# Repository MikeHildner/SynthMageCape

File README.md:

# Synth Mage Cape

An LED stage cape for a keyboard player. The lights follow what is played: a
small controller in a belt pouch listens to the keyboard over Bluetooth MIDI
and drives addressable LEDs on the lapels, the collar, the shoulders, and
strings of small lights below the lapels.

The picture is a concept render, not a photograph. A short video of the real
lights on a stand-in cape, following the keyboard: https://youtu.be/IYe8foX2Wks

## Where the project stands (November 2026)

- **Working:** the controller, the firmware, and every light, as a prototype
  on a stand-in cape.
- **Not made yet:** the cape itself. The sheet for the cape maker is
  [docs/designer-handoff.md](docs/designer-handoff.md).
- **Still changing.** This is the record of one build in progress, by a
  software developer who was new to electronics when it started. It is not a
  tested kit. Check the wiring, the power and your own parts before you copy
  anything.

## How it works

- **Keyboard:** a Korg Kronos with a CME WIDI Master in its MIDI OUT, which
  sends what is played as Bluetooth MIDI. Any keyboard that sends Bluetooth
  MIDI should do.
- **Controller:** an ESP32-S3 DevKitC-1 (N16R8) on a small board with a
  74AHCT125 level shifter, powered by a USB power bank. Four data outputs.
- **Lights:**
  - each lapel: two strips of 48 WS2812B LEDs (60 per metre), side by side
  - below each lapel: a string of 50 small WS2812B lights on thin wire,
    chained after the lapel
  - collar: a COB strip (160 per metre), 128 segments
  - each shoulder: two strips of 12 LEDs, side by side
- **Brightness is kept low on purpose.** The cape is for a dark stage, and the
  firmware has a hard ceiling (`MAX_BRIGHTNESS` in `Cape.h`).

What the lights do when you play:

| You do | The cape shows |
|---|---|
| Strike a key | A ripple on the lapels at that key's height. Harder is brighter. The colour is the note name. |
| Hold a key, or use the sustain pedal | A low glow stays on that row |
| Play a low note | The ripple runs off the bottom of the lapel as a dot along the string |
| Play a high note | The ripple runs off the top of the lapel and crosses the shoulders |
| Play several notes | The collar shows one band per sounding note |
| Bend the pitch | The colour of everything lit turns |
| Add vibrato (mod wheel) | The colours swing to and fro |

## What is in the repository

| Folder | What it holds |
|---|---|
| [firmware/cape-midi](firmware/cape-midi) | The firmware (PlatformIO, Arduino framework, FastLED, NimBLE). Start with [firmware/README.md](firmware/README.md). |
| [hardware/shifter-board](hardware/shifter-board) | The level shifter and power distribution board: KiCad files and Gerbers |
| [hardware/perfboard-4](hardware/perfboard-4) | The same circuit laid out for perfboard, which is what the prototype runs on |
| [hardware/enclosure](hardware/enclosure) | A printable box for the controller (OpenSCAD and STL) |
| [docs/electronics-spec.md](docs/electronics-spec.md) | The electronics plan and its test log. Parts of the plan are older than the build; where the two disagree, the firmware and the handoff are newer. |
| [docs/shopping-list.md](docs/shopping-list.md) | Parts and tools, with the reasons for each choice |
| [docs/bench-session-1.md](docs/bench-session-1.md), [docs/perfboard-4-build.md](docs/perfboard-4-build.md) | Step-by-step build guides for the controller board |
| [docs/designer-handoff.md](docs/designer-handoff.md) | What the garment needs from the electronics, written for whoever sews the cape (also as a PDF) |
| [docs/render-prompts.md](docs/render-prompts.md), [docs/renders](docs/renders) | The concept renders and the prompts that made them |
| [apps/midi-monitor-android](apps/midi-monitor-android) | A small Android app that shows what a Bluetooth MIDI device sends. Useful for finding out what your own keyboard sends. |
| [wled](wled) | Settings from the first phase, when the controller ran WLED |
| [tools](tools) | Scripts: build and update the firmware, generate the board drawings and the handoff PDF |

## Building the firmware

1. Install [PlatformIO Core](https://platformio.org/install/cli).
2. In `firmware/cape-midi/include`, copy `secrets.example.h` to `secrets.h`
   and fill in your Wi-Fi name and password. The cape uses Wi-Fi at home only,
   for updates and a status page; away from home it runs on Bluetooth alone.
   `secrets.h` is ignored by git.
3. From `firmware/cape-midi`, run `pio run -t upload` with the board on USB.

`tools\pio.cmd` and `tools\ota.cmd` are Windows helpers for my own setup (one
works around an antivirus certificate problem, the other sends an update over
Wi-Fi to my cape's address). [firmware/README.md](firmware/README.md) explains
both.

## Licence

MIT. See [LICENSE](LICENSE).

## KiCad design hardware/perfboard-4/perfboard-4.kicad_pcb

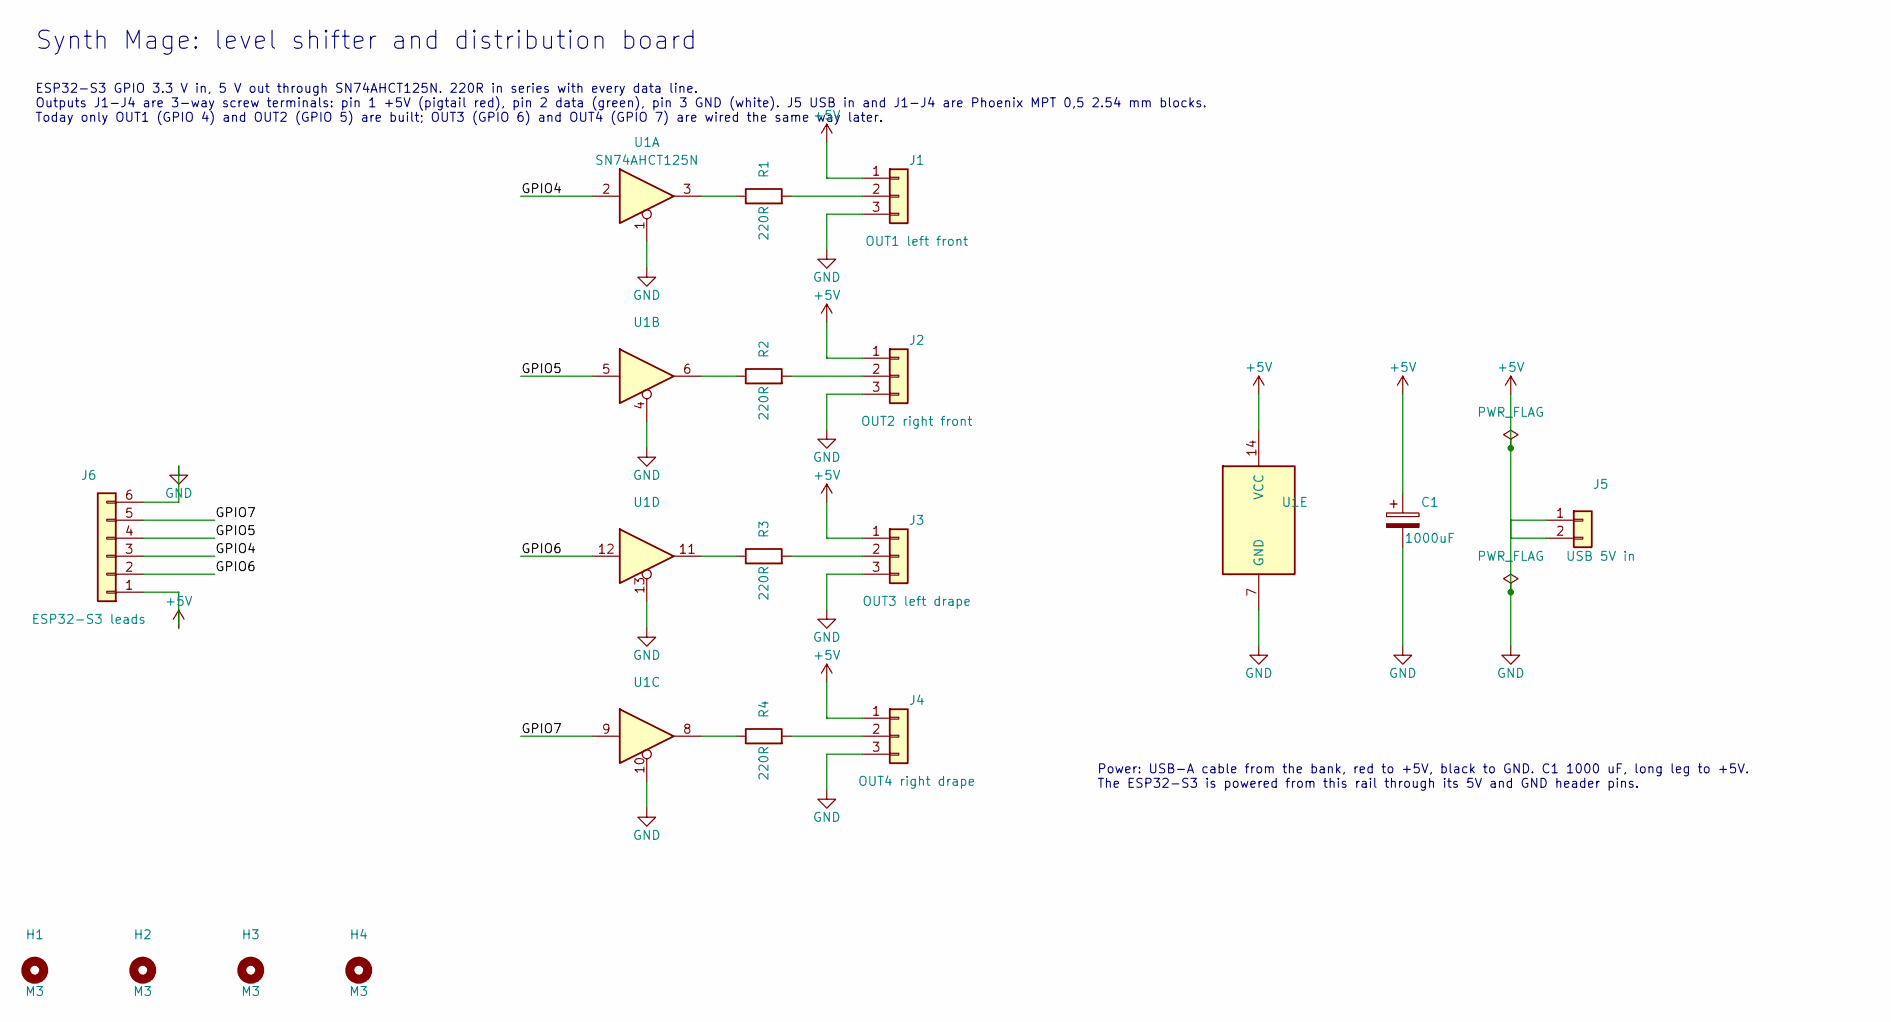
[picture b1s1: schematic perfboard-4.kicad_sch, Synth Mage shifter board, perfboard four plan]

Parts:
C1: 1000uF; CP_Radial_D10.0mm_P5.00mm
H1, H2, H3, H4: M3; MountingHole_2.2mm_M2
J1: OUT1 left front; Pigtail_3wire
J2: OUT2 right front; Pigtail_3wire
J3: OUT3 left drape; Pigtail_3wire
J4: OUT4 right drape; Pigtail_3wire
J5: USB 5V in; USB_2wire
J6: ESP32-S3 leads; ESP_6wire
R1, R2, R3, R4: 220R; R_Axial_DIN0207_L6.3mm_D2.5mm_P7.62mm_Horizontal
U1: SN74AHCT125N; DIP-14_W7.62mm_Socket

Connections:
+5V: C1.1, J1.1, J2.1, J3.1, J4.1, J5.2, J6.1, U1.14 (VCC)
/GPIO4: J6.3, U1.2
/GPIO5: J6.4, U1.5
/GPIO6: J6.2, U1.12
/GPIO7: J6.5, U1.9
GND: C1.2, J1.3, J2.3, J3.3, J4.3, J5.1, J6.6, U1.1, U1.4, U1.7 (GND), U1.10, U1.13
unnamed: J1.2, R1.2
unnamed: J2.2, R2.2
unnamed: J3.2, R3.2
unnamed: J4.2, R4.2
unnamed: R1.1, U1.3
unnamed: R2.1, U1.6
unnamed: R3.1, U1.11
unnamed: R4.1, U1.8

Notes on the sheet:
Synth Mage: level shifter and distribution board
ESP32-S3 GPIO 3.3 V in, 5 V out through SN74AHCT125N. 220R in series with every data line. Outputs J1-J4 are 3-way screw terminals: pin 1 +5V (pigtail red), pin 2 data (green), pin 3 GND (white). J5 USB in and J1-J4 are Phoenix MPT 0,5 2.54 mm blocks. Today only OUT1 (GPIO 4) and OUT2 (GPIO 5) are 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
Power: USB-A cable from the bank, red to +5V, black to GND. C1 1000 uF, long leg to +5V. The ESP32-S3 is powered from this rail through its 5V and GND header pins.

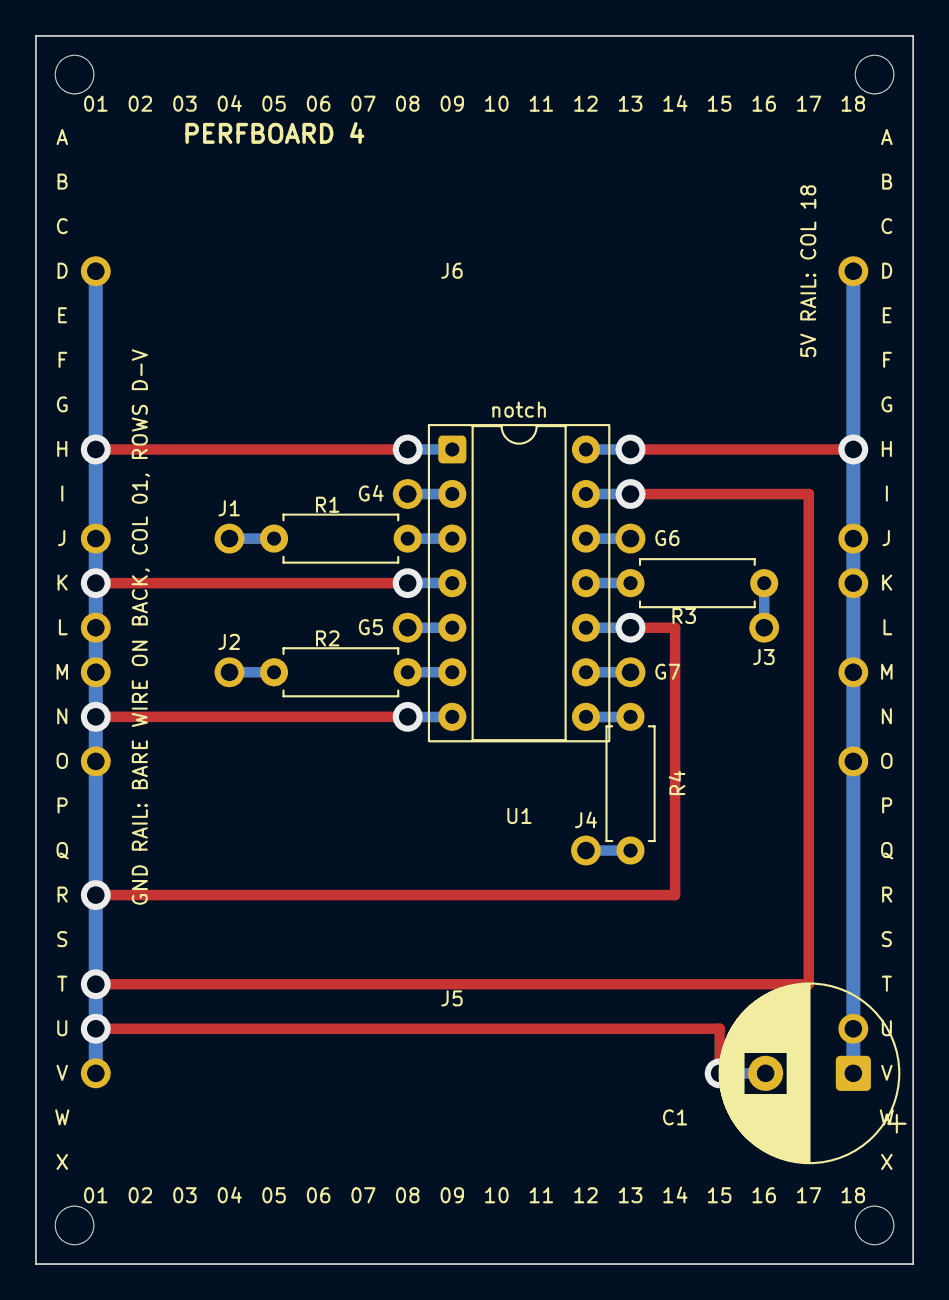
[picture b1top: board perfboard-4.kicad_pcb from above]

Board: 2 copper layers, 50.0 x 70.0 mm, 16 parts (0 on the bottom side), 14 nets.

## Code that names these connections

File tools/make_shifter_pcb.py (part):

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ds.SetCopperLayerCount(2)

# ------------------------------------------------------------------ nets
NET_NAMES = ["+5V", "GND", "/GPIO4", "/GPIO5", "/GPIO6", "/GPIO7",
             "Net-(J1-Pin_2)", "Net-(J2-Pin_2)", "Net-(J3-Pin_2)", "Net-(J4-Pin_2)",
             "Net-(R1-Pad1)", "Net-(R2-Pad1)", "Net-(R3-Pad1)", "Net-(R4-Pad1)"]
nets = {}
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PAD_NETS = {
    ("U1", "14"): "+5V", ("U1", "7"): "GND", ("U1", "1"): "GND", ("U1", "4"): "GND",
    ("U1", "10"): "GND", ("U1", "13"): "GND",
    ("U1", "2"): "/GPIO4", ("U1", "5"): "/GPIO5", ("U1", "12"): "/GPIO6", ("U1", "9"): "/GPIO7",
    ("U1", "3"): "Net-(R1-Pad1)", ("U1", "6"): "Net-(R2-Pad1)", ("U1", "11"): "Net-(R3-Pad1)", ("U1", "8"): "Net-(R4-Pad1)",
    ("R1", "1"): "Net-(R1-Pad1)", ("R1", "2"): "Net-(J1-Pin_2)",
    ("R2", "1"): "Net-(R2-Pad1)", ("R2", "2"): "Net-(J2-Pin_2)",
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    ("J3", "1"): "+5V", ("J3", "2"): "Net-(J3-Pin_2)", ("J3", "3"): "GND",
    ("J4", "1"): "+5V", ("J4", "2"): "Net-(J4-Pin_2)", ("J4", "3"): "GND",
    ("J5", "1"): "GND", ("J5", "2"): "+5V",
    ("J6", "1"): "+5V", ("J6", "2"): "/GPIO6", ("J6", "3"): "/GPIO4", ("J6", "4"): "/GPIO5", ("J6", "5"): "/GPIO7", ("J6", "6"): "GND",
    ("C1", "1"): "+5V", ("C1", "2"): "GND",
}

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    x, y = pad(j, 1)
    track("+5V", F, 0.6, (BUS_X, y + 1.5), (x + 0.5, y + 1.5), (x, y + 1.0), (x, y))

# inputs on the top layer: GPIO4 -> pin 2, GPIO5 -> pin 5 (both on the chip's left column)
track("/GPIO4", F, SIG, pad("J6", 3), (9.0, pad("J6", 3)[1]), (13.54, pad("U1", 2)[1]), pad("U1", 2))
track("/GPIO5", F, SIG, pad("J6", 4), (14.46, pad("J6", 4)[1]), (15.0, pad("U1", 5)[1]), pad("U1", 5))
# inputs on the bottom layer, passing between the chip's pads: GPIO6 -> pin 12, GPIO7 -> pin 9 (right column)
track("/GPIO6", B, THIN, pad("J6", 2), (9.0, pad("J6", 2)[1]), (9.73, 15.31), (25.35, 15.31), pad("U1", 12))
track("/GPIO7", B, THIN, pad("J6", 5), (10.0, pad("J6", 5)[1]), (11.81, 25.47), (25.35, 25.47), pad("U1", 9))
# outputs from the left column cross under the chip on the bottom layer to R1 and R2
track("Net-(R1-Pad1)", B, THIN, pad("U1", 3), (20.27, 17.85), (28.0, 17.85), (RX, 15.85), pad("R1", 1))
track("Net-(R2-Pad1)", B, THIN, pad("U1", 6), (20.27, 22.93), (28.0, 22.93), (28.23, ROWS["R2"]), pad("R2", 1))
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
